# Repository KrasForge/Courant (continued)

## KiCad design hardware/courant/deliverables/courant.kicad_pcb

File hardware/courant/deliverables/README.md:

> **Release synchronization: 2026-09-16.** Current native boards, fabrication-format exports and CAD are indexed in `../../RELEASE_SYNC_STATUS.md`. Earlier statements below about pre-repair exports are historical; electrical/physical validation limitations still apply.

# Current native mainboard — 2026-09-16

| Top (F.Cu, faces the panel) | Bottom (B.Cu) |
| --- | --- |
|  |  |

<sub>Rendered from `courant.kicad_pcb` by `docs/media/scripts/`. Component bodies in the 3D view are simplified stand-ins. See `docs/media/README.md`.</sub>

The PCB in this folder passes Backplane KiCad 10.0.6 DRC: **0 errors, 0 warnings, 0 unconnected**, with unchanged project rules. Current counts: **2,158 track segments and 299 vias**. See `MAINBOARD_REPAIR.md` and `native_checks/drc.json`.

The assembly STEP, mechanical PDF/DXF, `dist/` PCB copies, 2D views, Gerbers, drills, placement data, BOM/netlist metadata and `dist/courant-fab.zip` have been regenerated from the current repaired native board. Use `hardware/refresh_outputs.py` for future review-export refreshes. Legacy route/reconstruction scripts are guarded from overwriting the authoritative native PCB.

**Not a manufacturing approval.** Component/footprint sign-off, FPGA operation/timing, electrical power integrity, thermal/fault behavior and physical assembly remain separate release gates.

The original handoff notes below are preserved as historical information; their old track/via counts are superseded above.

---

# Courant Rev A — handoff package

Standalone Artix-7 instrument board. **160 × 100 mm** on the Edge.Cuts
centreline (160.1 × 100.1 measured over the 0.1 mm stroke), 6 layers, 1.6 mm.
Four NPTH 3.2 mm mounting holes at (25,55), (175,55), (25,145), (175,145) —
150 × 90 mm spacing.
Routed and native-checked: **0 DRC errors, 0 warnings, 0 unconnected**, 2158 track segments,
4386.2 mm of copper, 299 vias, both ground planes uncut.

| File | What it is |
| --- | --- |
| `courant.kicad_pcb` | the board. KiCad 10 |
| `courant.kicad_pro` | project file — **open it alongside the board or you get KiCad's default design rules, not this board's** |
| `courant-assembly.step` | populated assembly, 3D. Board body, copper, silkscreen, soldermask and 183 of 202 component bodies |
| `courant-bom.csv` | bill of materials, 57 line items / 183 placements |
| `courant-netlist.txt` | 96 nets, extracted from the routed board |
| `courant-panel-interface.csv` | pinout of all 15 headers — the spec for building the front panel |
| `courant-mechanical.pdf` | outline, fabrication layer, silkscreen |
| `courant-outline.dxf` | board outline for mechanical CAD |
| `courant-schematic.svg` | schematic — 183 components, 739 pins, 532 wires, 248 net labels, 7038 x 6958 px vector |
| `courant-panel-hardware.md` | off-board parts, with `datasheets/` alongside |
| `courant-eurorack.md` | Eurorack status: what works as built, what changes, with values |
| `courant-source-design.ts` | the design source |

## Design rules

Default 0.15 mm track / 0.15 mm clearance, vias 0.55 / 0.25 mm. Power class
0.40 mm track, Ground 0.30 mm. These are set by the FTG256's 1.0 mm ball pitch:
escaping between two balls needs width + 2 × clearance inside a 0.5 mm gap, and
0.15 + 0.30 = 0.45 mm fits where KiCad's 0.2 mm defaults (0.6 mm) cannot.
0.25 mm drill through 1.6 mm is a 6.4:1 aspect ratio — inside any standard
6-layer process.

## Notes on three of these

**The schematic is rendered by `scripts/schematic.py`, not by tscircuit.**
`tsci export -f schematic-svg` and `-f schematic-pdf` both emit a near-empty
sheet for this design — about ten kilobytes, twenty text elements for two
hundred components — while the circuit JSON behind them holds all 183
components, 739 ports and 532 traces. The data was never missing, only the
drawing, so the drawing is done here. It is complete and to scale; it is not
arranged for signal flow, because tscircuit places symbols in declaration
order and no autolayout turns that into a drafted sheet.

**Every placement has a manufacturer part number**, and each one was checked
against live stock rather than inferred. Two families are covered by one
verified member plus the manufacturer's own value coding, noted on the line:
the Murata C0G run and the Yageo RC0603FR series.

**The panel hardware in `courant-panel-hardware.md` is a proposal.** The design
names no off-board parts and the right ones depend on a panel format that does
not exist yet, so those selections are specified to be electrically correct and
mechanically ordinary — a starting BOM, not a decision already taken. The four
that are sourced have datasheets in `datasheets/`.

## One design fix made while preparing this

R10 was **25 kΩ**, which is on no E-series grid and is not a stocked 1 % part —
a search for it returns 24.9 kΩ. It sets the V1 rail through the TPS62130's
0.8 V reference, so it is now **24.9 kΩ**: 0.8 x (1 + 24.9/100) = 0.9992 V
against a 1.000 V target, nearer than the 1 % resistors can hold. Fixed in
`design.ts` and in the board; `npm run check` passes.

## Before ordering

U1 is **XC7A50T-1FTG256I**, swapped from the XC7A35T-1FTG256C. The pin
compatibility is verified, not assumed: AMD's package files for the two parts
in FTG256 — both kept in `reference/` — are byte-identical from line 2 to the
end. All 256 balls, their banks, I/O types and no-connect flags match; the only
difference in either file is the device name on the header line. That makes the
swap a part number and nothing else, and it is the cheaper part besides
($67.01 against $118.75 at JLCPCB, both in stock) with 57% more logic and an
industrial temperature range.

One check is still worth doing and cannot be done from here: a Vivado synthesis
run against the A50T using the generated `courant_rev_a.xdc`. It will reject
any invalid ball assignment outright, and it confirms timing still closes —
the speed grade is unchanged at -1, so it should.

## Native repair and current files

See `../../REPAIR_STATUS.md` and `../reports/native/`. The local `RadianMain.pretty` snapshots and `fp-lib-table` must travel with the board. Both routed board copies and the manufacturing-format review exports were replaced on 2026-09-16. Native checks are not electrical or physical product validation.

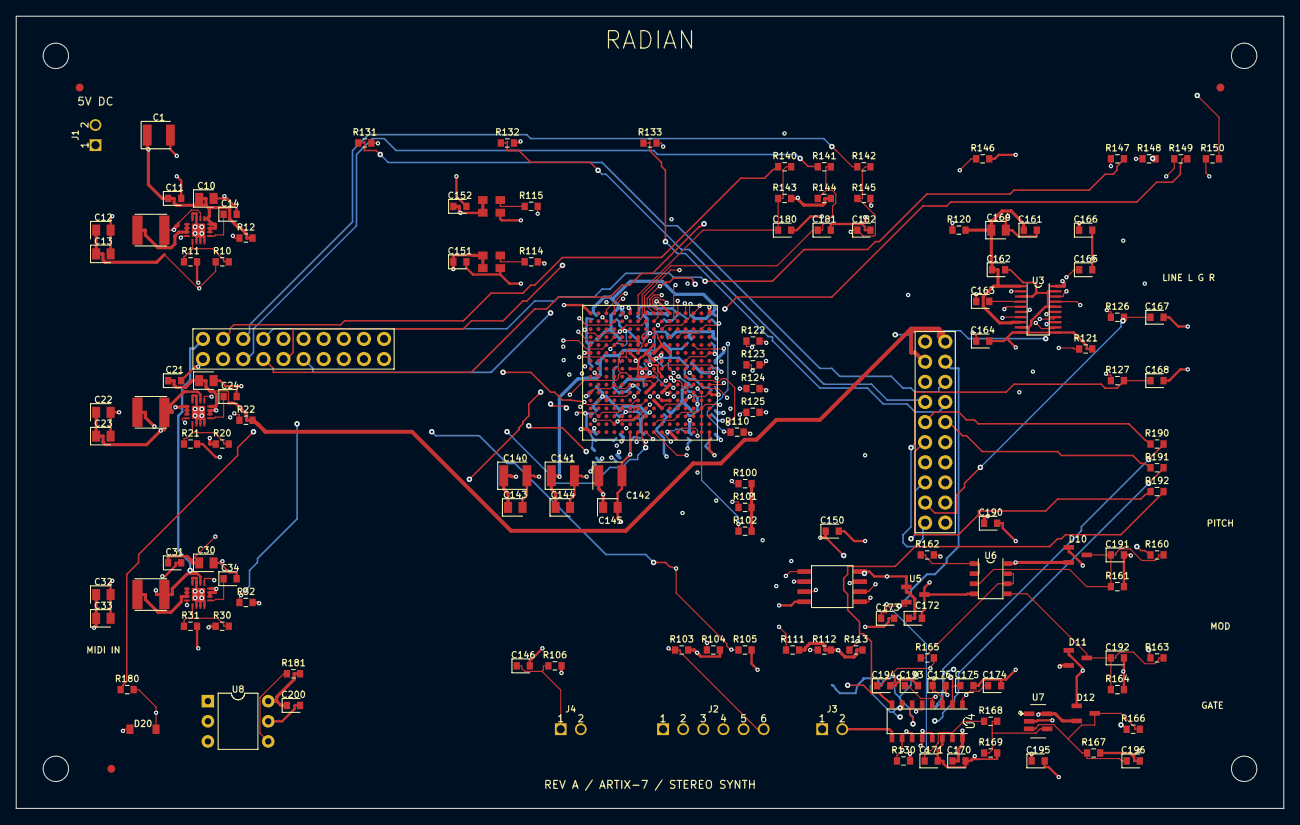
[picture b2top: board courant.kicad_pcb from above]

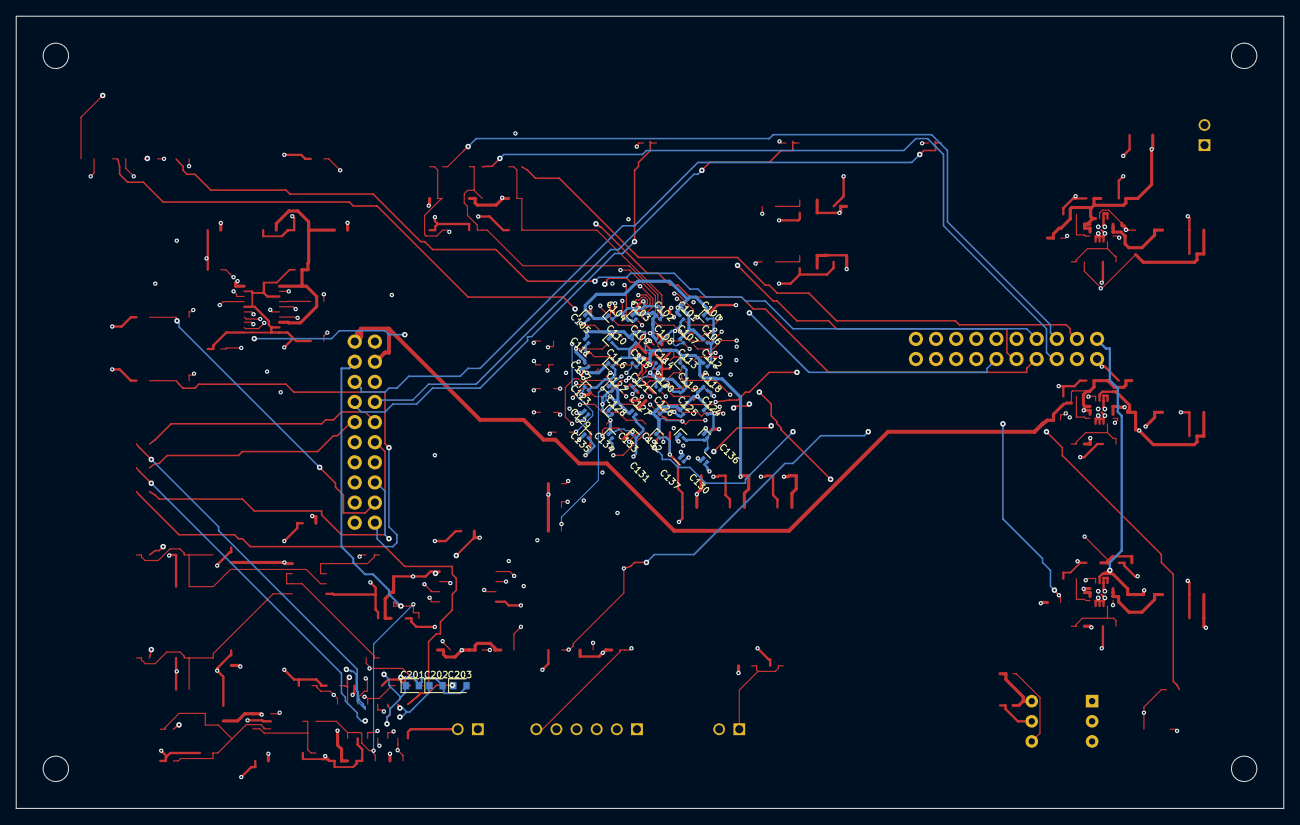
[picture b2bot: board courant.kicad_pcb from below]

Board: 6 copper layers, 160.0 x 100.0 mm, 180 parts (41 on the bottom side), 102 nets.

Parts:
C1, C140, C141: 47uF; C_1210_3225Metric_A
C10, C20, C30, C160: 10uF; C_0805_2012Metric_B
C11, C21, C31, C146, C150, C151, C152, C161, C162, C166, C170, C172, C190, C195, C200: 100nF; C_0603_1608Metric_Radian
C12, C22, C32: 22uF; C_0805_2012Metric_A
C13, C23, C33: 22uF; C_0805_2012Metric_B
C14, C24, C34: 3.3nF; C_0603_1608Metric_Radian
C100, C103, C104, C110, C113, C116, C120, C122, C128: 100nF; C_0201_0603Metric_C
C101, C102, C106, C107, C108, C109, C112, C114, C115, C118, C119, C121, C124, C125, C126, C127, C136: 100nF; C_0201_0603Metric_D
C105, C123, C130, C131, C132, C133, C134, C135: 100nF; C_0201_0603Metric_E
C111, C117, C129: 100nF; C_0201_0603Metric_A
C137: 100nF; C_0201_0603Metric_B
C142: 47uF; C_1210_3225Metric_B
C143, C144: 4.7uF; C_0805_2012Metric_B
C145: 4.7uF; C_0805_2012Metric_A
C163, C164: 2.2uF; C_0603_1608Metric_Radian
C165, C171, C173: 1uF; C_0603_1608Metric_Radian
C167, C168: 2.2nF; C_0603_1608Metric_Radian
C174, C175, C176, C180, C181, C182, C193, C194, C201, C202, C203: 10nF; C_0603_1608Metric_Radian
C191, C192, C196: 1nF; C_0603_1608Metric_Radian
D10, D11, D12: BAT54S; Nexperia_BAT54S_215_SOT23
D20: 1N4148W; Diodes_1N4148W_7_F_SOD123
J1: 22-23-2021; Molex_22_23_2021_RowY
J2: 22-23-2061; Molex_22_23_2061
J3, J4: 22-23-2021; Molex_22_23_2021_RowX
J17, J18: IPT1-110-06-L-D; Samtec_IPT1_110_06_L_D
L1, L2, L3: 1µH; Changjiang_FNR4030S1R0MT
R10: 24.9kΩ; R_0603_1608Metric_Radian
R11, R21, R31, R166: 100kΩ; R_0603_1608Metric_Radian
R12, R22, R32, R103, R104, R105, R106, R121, R130, R143, R144, R145, R146, R169: 10kΩ; R_0603_1608Metric_Radian
R20: 124kΩ; R_0603_1608Metric_Radian
R30: 316kΩ; R_0603_1608Metric_Radian
R100, R101, R102, R111, R112, R113: 4.7kΩ; R_0603_1608Metric_Radian
R110, R114, R115, R122, R123, R124, R125: 33Ω; R_0603_1608Metric_Radian
R120: 1Ω; R_0603_1608Metric_Radian
R126, R127: 470Ω; R_0603_1608Metric_Radian
R131, R132, R133, R140, R141, R142, R147, R148, R149, R150, R190, R191, R192: 1kΩ; R_0603_1608Metric_Radian
R160, R161, R163, R164: 20kΩ; R_0603_1608Metric_Radian
R162, R165: 100Ω; R_0603_1608Metric_Radian
R167: 33kΩ; R_0603_1608Metric_Radian
R168: 40.2kΩ; R_0603_1608Metric_Radian
R180: 220Ω; R_0603_1608Metric_Radian
R181: 2.2kΩ; R_0603_1608Metric_Radian
U1: XC7A50T-1FTG256I; XC7A50T_1FTG256I_FTG256
U2: W25Q64JVSSIQ; W25Q64JVSSIQ_SOIC8_208mil
U3: PCM5102APWR; PCM5102APWR_TSSOP20
U4: MCP3208-CI/SL; MCP3208_CI_SL_SOIC16
U5: REF3125AIDBZR; REF3125AIDBZR_SOT23
U6: MCP6002-I/SN; MCP6002_I_SN_SOIC8
U7: MCP6561T-E/OT; MCP6561T_E_OT_SOT23_5
U8: H11L1M; H11L1M_DIP6
U11, U12, U13: TPS62130ARGTR; TPS62130ARGTR_WQFN16
Y1: ASE-100.000MHZ-LC-T; Abracon_ASE_3225_4Pin
Y2: ASE-12.288MHZ-LC-T; Abracon_ASE_3225_4Pin

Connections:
A3V3: C160.1, C161.1, C162.1, R120.2, U3.1, U3.8
CLK100_RAW: R114.1, Y1.3
DAC_CAPM: C163.2, U3.4
DAC_CAPP: C163.1, U3.2
DAC_L: R126.1, U3.6
DAC_LDO: C165.1, U3.18
DAC_R: R127.1, U3.7
DAC_VNEG: C164.1, U3.5
DONE: R101.1, U1.122
ENC_A_RAW: J18.4, R140.1
ENC_B_RAW: J18.5, R141.1
ENC_SW_RAW: J18.6, R142.1
FB1: R10.2, R11.1, U11.5
FB2: R20.2, R21.1, U12.5
FB3: R30.2, R31.1, U13.5
FLASH_CLK: R110.2, U2.6
FLASH_CLK_RAW: R110.1, U1.72
FLASH_CS: R111.1, U1.172, U2.1
FLASH_HOLD: R113.1, U1.160, U2.7
FLASH_MISO: U1.142, U2.2
FLASH_MOSI: U1.141, U2.5
FLASH_WP: R112.1, U1.159, U2.3
GATE_DIV: C196.1, D12.3, R166.2, R167.1, U7.3
GATE_IN: J17.15, R166.1
GATE_REF: R168.2, R169.1, U7.4
GND: C1.2, C10.2, C11.2, C12.2, C13.2, C14.2, C20.2, C21.2, C22.2, C23.2, C24.2, C30.2, C31.2, C32.2, C33.2, C34.2, C100.2, C101.2, C102.2, C103.2, C104.2, C105.2, C106.2, C107.2, C108.2, C109.2, C110.2, C111.2, C112.2, C113.2, C114.2, C115.2, C116.2, C117.2, C118.2, C119.2, C120.2, C121.2, C122.2, C123.2, C124.2, C125.2, C126.2, C127.2, C128.2, C129.2, C130.2, C131.2, C132.2, C133.2, C134.2, C135.2, C136.2, C137.2, C140.2, C141.2, C142.2, C143.2, C144.2, C145.2, C146.2, C150.2, C151.2, C152.2, C160.2, C161.2, C162.2, C164.2, C165.2, C166.2, C167.2, C168.2, C170.2, C171.2, C172.2, C173.2, C174.2, C175.2, C176.2, C180.2, C181.2, C182.2, C190.2, C191.2, C192.2, C193.2, C194.2, C195.2, C196.2, C200.2, C201.2, C202.2, C203.2, D10.1, D11.1, D12.1, J1.2, J2.2, J3.2, J4.2, J17.1, J17.5, J17.12, J17.16, J17.18, J17.20, J18.1, J18.3, J18.12, R11.2, R21.2, R31.2, R105.2, R121.2, R146.2, R161.2, R164.2, R167.2, R169.2, U1.1, U1.11, U1.24, U1.37, U1.47, U1.50, U1.60, U1.73, U1.86, U1.88, U1.90, U1.96, U1.99, U1.103, U1.105, U1.109, U1.118, U1.119, U1.120, U1.135, U1.136, U1.137, U1.139, U1.148, U1.150, U1.158, U1.161, U1.171, U1.184, U1.186, U1.187, U1.197, U1.207, U1.210, U1.220, U1.233, U1.246, U1.256, U2.4, U3.3, U3.9, U3.10, U3.11, U3.16, U3.19, U4.9, U4.14, U5.3, U6.4, U7.2, U8.5, U11.6, U11.7, U11.8, U11.15, U11.16, U11.17, U12.6, U12.7, U12.8, U12.15, U12.16, U12.17, U13.6, U13.7, U13.8, U13.15, U13.16, U13.17, Y1.2, Y2.2
I2S_BCLK: R123.2, U3.13
I2S_DATA: R125.2, U3.14
I2S_LRCLK: R124.2, U3.15
I2S_MCLK: R122.2, U3.12
INIT_B: R100.1, U1.154
JTAG_TCK: J2.3, J18.17, R105.1, U1.167
JTAG_TDI: J2.5, J18.19, R104.1, U1.199
JTAG_TDO: J2.4, J18.18, U1.200
JTAG_TMS: J2.6, J18.20, R103.1, U1.183
LED0_A: J18.8, R147.2
LED1_A: J18.9, R148.2
LED2_A: J18.10, R149.2
LED3_A: J18.11, R150.2
LINE_L: C167.1, J17.17, R126.2
LINE_R: C168.1, J17.19, R127.2
MCLK_RAW: R115.1, Y2.3
MIDI4: J18.13, R180.1
MIDI5: D20.1, J18.14, U8.2
MIDI_A: D20.2, R180.2, U8.1
MOD_ADC: C194.1, R165.2, U4.5
MOD_BUF: R165.1, U6.6, U6.7
MOD_DIV: C192.1, D11.3, R163.2, R164.1, U6.5
MOD_IN: J17.14, R163.1
PG1: R12.1, U11.4, U12.13
PG18: R22.1, U12.4, U13.13
PITCH_ADC: C193.1, R162.2, U4.4
PITCH_BUF: R162.1, U6.1, U6.2
PITCH_DIV: C191.1, D10.3, R160.2, R161.1, U6.3
PITCH_IN: J17.13, R160.1
POT_DECAY: C175.1, R132.2, U4.2
POT_DECAY_RAW: J17.7, R132.1
POT_DELAY: C202.1, R191.2, U4.7
POT_DELAY_RAW: J17.10, R191.1
POT_DRIVE: C201.1, R190.2, U4.6
POT_DRIVE_RAW: J17.9, R190.1
POT_PITCH: C174.1, R131.2, U4.1
POT_PITCH_RAW: J17.6, R131.1
POT_REVERB: C203.1, R192.2, U4.8
POT_REVERB_RAW: J17.11, R192.1
POT_TIMBRE: C176.1, R133.2, U4.3
POT_TIMBRE_RAW: J17.8, R133.1
PROGRAM_B: J3.1, J18.15, R32.1, U1.169, U13.4
PUDC_B: R102.1, U1.175
SS1: C14.1, U11.9
SS2: C24.1, U12.9
SS3: C34.1, U13.9
SW1: L1.1, U11.1, U11.2, U11.3
SW2: L2.1, U12.1, U12.2, U12.3
SW3: L3.1, U13.1, U13.2, U13.3
V1: C12.1, C13.1, C100.1, C101.1, C102.1, C103.1, C104.1, C105.1, C106.1, C107.1, C108.1, C140.1, C143.1, L1.2, R10.1, U1.74, U1.87, U1.89, U1.91, U1.102, U1.121, U1.134, U1.153, U1.168, U11.14
V1V8: C22.1, C23.1, C109.1, C110.1, C111.1, C112.1, C113.1, C141.1, C144.1, L2.2, R20.1, U1.104, U1.106, U1.138, U1.155, U1.170, U12.14
V3V3: C32.1, C33.1, C114.1, C115.1, C116.1, C117.1, C118.1, C119.1, C120.1, C121.1, C122.1, C123.1, C124.1, C125.1, C126.1, C127.1, C128.1, C129.1, C130.1, C131.1, C132.1, C133.1, C134.1, C135.1, C136.1, C137.1, C142.1, C145.1, C150.1, C151.1, C152.1, C166.1, C170.1, C172.1, C190.1, C195.1, C200.1, D10.2, D11.2, D12.2, J2.1, J18.2, L3.2, R30.1, R32.2, R100.2, R101.2, R102.2, R103.2, R104.2, R106.2, R111.2, R112.2, R113.2, R120.1, R130.2, R143.2, R144.2, R145.2, R181.2, U1.6, U1.16, U1.19, U1.29, U1.42, U1.55, U1.68, U1.71, U1.78, U1.81, U1.127, U1.130, U1.140, U1.166, U1.176, U1.179, U1.185, U1.189, U1.202, U1.215, U1.228, U1.238, U1.241, U1.251, U2.8, U3.20, U4.16, U5.1, U6.8, U7.5, U8.6, U13.14, Y1.1, Y1.4, Y2.1, Y2.4
VIN5: C1.1, C10.1, C11.1, C20.1, C21.1, C30.1, C31.1, J1.1, J17.2, J17.3, R12.2, R22.2, U11.10, U11.11, U11.12, U11.13, U12.10, U12.11, U12.12, U13.10, U13.11, U13.12
VREF25: C171.1, C173.1, J17.4, R168.1, U4.15, U5.2
adc_cs_n: R130.1, U1.5, U4.10
adc_miso: U1.4, U4.12
adc_mosi: U1.20, U4.11
adc_sclk: U1.3, U4.13
audio_mclk_in: R115.2, U1.67
clk100: R114.2, U1.52
cv_select: J18.7, R146.1, U1.9
dac_bclk: R123.1, U1.248
dac_data: R125.1, U1.250
dac_lrclk: R124.1, U1.249
dac_mclk: R122.1, U1.247
dac_unmute: R121.1, U1.252, U3.17
enc_a: C180.1, R140.2, R143.1, U1.7
enc_b: C181.1, R141.2, R144.1, U1.23
enc_btn_n: C182.1, R142.2, R145.1, U1.8
gate: U1.10, U7.1
led0: R147.1, U1.12
led1: R148.1, U1.28
led2: R149.1, U1.13
led3: R150.1, U1.14
midi_rx: R181.1, U1.25, U8.4
reset_n: C146.1, J4.1, J18.16, R106.1, U1.26

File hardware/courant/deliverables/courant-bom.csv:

Reference(s),Qty,Value,Footprint,Side,Manufacturer,MPN,LCSC,Notes
"C101,C102,C106,C107,C108,C109,C112,C114,C115,C118,C119,C121,C124,C125,C126,C127,C136",17,100nF,RadianMain:C_0201_0603Metric_D,bottom,CCTC,TCC0201X5R104K100ZT,C5142565,10 V X5R. JLC extended library: one setup fee for the whole array
"C11,C21,C31,C146,C150,C151,C152,C161,C162,C166,C170,C172,C190,C195,C200",15,100nF,RadianMain:C_0603_1608Metric_Radian,top,Samsung,CL10B104KB8NNNC,C1591,50 V X7R
"R12,R22,R32,R103,R104,R105,R106,R121,R130,R143,R144,R145,R146,R169",14,10kΩ,RadianMain:R_0603_1608Metric_Radian,top,Yageo,RC0603FR-0710KL,C98220,thick film 1%
"R131,R132,R133,R140,R141,R142,R147,R148,R149,R150,R190,R191,R192",13,1kΩ,RadianMain:R_0603_1608Metric_Radian,top,Yageo,RC0603FR-071KL,,thick film 1%
"C100,C103,C104,C110,C113,C116,C120,C122,C128",9,100nF,RadianMain:C_0201_0603Metric_C,bottom,CCTC,TCC0201X5R104K100ZT,C5142565,10 V X5R. JLC extended library: one setup fee for the whole array
"C105,C123,C130,C131,C132,C133,C134,C135",8,100nF,RadianMain:C_0201_0603Metric_E,bottom,CCTC,TCC0201X5R104K100ZT,C5142565,10 V X5R. JLC extended library: one setup fee for the whole array
"C174,C175,C176,C180,C181,C182,C193,C194",8,10nF,RadianMain:C_0603_1608Metric_Radian,top,Murata,GRM1885C1H103JA01D,C85973,"50 V C0G -- ADC anti-alias, C0G for low voltage coefficient"
"R110,R114,R115,R122,R123,R124,R125",7,33Ω,RadianMain:R_0603_1608Metric_Radian,top,Yageo,RC0603FR-0733RL,,thick film 1%
"R100,R101,R102,R111,R112,R113",6,4.7kΩ,RadianMain:R_0603_1608Metric_Radian,top,Yageo,RC0603FR-074K7L,,thick film 1%
"R11,R21,R31,R166",4,100kΩ,RadianMain:R_0603_1608Metric_Radian,top,Yageo,RC0603FR-07100KL,,thick film 1%
"C10,C20,C30,C160",4,10uF,RadianMain:C_0805_2012Metric_B,top,Samsung,CL21A106KAYNNNE,C15850,"25 V X5R, JLC basic library"
"R160,R161,R163,R164",4,20kΩ,RadianMain:R_0603_1608Metric_Radian,top,Yageo,RT0603BRD0720KL,C723637,"0.1%, 25 ppm/C thin film -- matched CV divider pair"
"C111,C117,C129",3,100nF,RadianMain:C_0201_0603Metric_A,bottom,CCTC,TCC0201X5R104K100ZT,C5142565,10 V X5R. JLC extended library: one setup fee for the whole array
"C201,C202,C203",3,10nF,RadianMain:C_0603_1608Metric_Radian,bottom,Murata,GRM1885C1H103JA01D,C85973,"50 V C0G -- ADC anti-alias, C0G for low voltage coefficient"
"C191,C192,C196",3,1nF,RadianMain:C_0603_1608Metric_Radian,top,Murata,GRM1885C1H102JA01D,,"50 V C0G, same series as the 10 nF"
"C165,C171,C173",3,1uF,RadianMain:C_0603_1608Metric_Radian,top,Samsung,CL10B105KB8NQNC,C5199872,50 V X7R
"L1,L2,L3",3,1µH,RadianMain:Changjiang_FNR4030S1R0MT,top,Changjiang Electronics,FNR4030S1R0MT,C167865,"4x4 mm shielded, 18 mOhm, 5.7 A sat -- must exceed the TPS62130's 3 A plus ripple"
"C13,C23,C33",3,22uF,RadianMain:C_0805_2012Metric_B,top,Samsung,CL21A226MAQNNNE,C45783,"25 V X5R, JLC basic library -- switcher output"
"C12,C22,C32",3,22uF,RadianMain:C_0805_2012Metric_A,top,Samsung,CL21A226MAQNNNE,C45783,"25 V X5R, JLC basic library -- switcher output"
"C14,C24,C34",3,3.3nF,RadianMain:C_0603_1608Metric_Radian,top,Murata,GRM1885C1H332JA01D,,50 V C0G -- switcher soft-start
"C1,C140,C141",3,47uF,RadianMain:C_1210_3225Metric_A,top,Murata,GRM32ER61C476KE15L,C77101,16 V X5R -- bulk input
"D10,D11,D12",3,BAT54S,RadianMain:Nexperia_BAT54S_215_SOT23,top,Nexperia,"BAT54S,215",,"Nexperia BAT54S,215; SOT-23 dual Schottky diode"
"U11,U12,U13",3,TPS62130ARGTR,RadianMain:TPS62130ARGTR_WQFN16,top,Texas Instruments,TPS62130ARGTR,,"3 A buck, QFN-16 with exposed pad"
"R162,R165",2,100Ω,RadianMain:R_0603_1608Metric_Radian,top,Yageo,RC0603FR-07100RL,,thick film 1%
"C167,C168",2,2.2nF,RadianMain:C_0603_1608Metric_Radian,top,Murata,GRM1885C1H222JA01D,,"50 V C0G, same series"
"C163,C164",2,2.2uF,RadianMain:C_0603_1608Metric_Radian,top,Samsung,CL10A225KO8NNNC,C23630,"16 V X5R, JLC basic library"
"C143,C144",2,4.7uF,RadianMain:C_0805_2012Metric_B,top,Yageo,CC0805KKX7R8BB475,C354262,25 V X7R
"R126,R127",2,470Ω,RadianMain:R_0603_1608Metric_Radian,top,Yageo,RC0603FR-07470RL,,thick film 1%
"J17,J18",2,IPT1-110-06-L-D,RadianMain:Samtec_IPT1_110_06_L_D,top,Samtec,IPT1-110-06-L-D,,2x10 2.54 mm vertical through-hole terminal strip; mates IPS1-110-01-L-D. Fully-mated PCB gap 19.99 mm; 20.45 mm max.
C137,1,100nF,RadianMain:C_0201_0603Metric_B,bottom,CCTC,TCC0201X5R104K100ZT,C5142565,10 V X5R. JLC extended library: one setup fee for the whole array
R20,1,124kΩ,RadianMain:R_0603_1608Metric_Radian,top,Yageo,RC0603FR-07124KL,,thick film 1%
D20,1,1N4148W,RadianMain:Diodes_1N4148W_7_F_SOD123,top,Diodes Incorporated,1N4148W-7-F,,Diodes Incorporated 1N4148W-7-F; SOD-123 fast switching diode
"J4,J3",2,22-23-2021,RadianMain:Molex_22_23_2021_RowX,top,Molex,22-23-2021,,KK 254 vertical friction-lock. Harness side: housing 22-01-3027 + 2 x 08-55-0102 crimp terminals
J1,1,22-23-2021,RadianMain:Molex_22_23_2021_RowY,top,Molex,22-23-2021,,KK 254 vertical friction-lock. Harness side: housing 22-01-3027 + 2 x 08-55-0102 crimp terminals
J2,1,22-23-2061,RadianMain:Molex_22_23_2061,top,Molex,22-23-2061,,KK 254 vertical friction-lock. Harness side: housing 22-01-3067 + 6 x 08-55-0102 crimp terminals
R120,1,1Ω,RadianMain:R_0603_1608Metric_Radian,top,Yageo,RC0603FR-071RL,,thick film 1%
R181,1,2.2kΩ,RadianMain:R_0603_1608Metric_Radian,top,Yageo,RC0603FR-072K2L,,thick film 1%
R180,1,220Ω,RadianMain:R_0603_1608Metric_Radian,top,Yageo,RC0603FR-07220RL,,thick film 1%
R10,1,24.9kΩ,RadianMain:R_0603_1608Metric_Radian,top,Yageo,RC0603FR-0724K9L,C137761,thick film 1%
R30,1,316kΩ,RadianMain:R_0603_1608Metric_Radian,top,Yageo,RC0603FR-07316KL,,thick film 1%
R167,1,33kΩ,RadianMain:R_0603_1608Metric_Radian,top,Yageo,RC0603FR-0733KL,,thick film 1%
C145,1,4.7uF,RadianMain:C_0805_2012Metric_A,top,Yageo,CC0805KKX7R8BB475,C354262,25 V X7R
R168,1,40.2kΩ,RadianMain:R_0603_1608Metric_Radian,top,Yageo,RC0603FR-0740K2L,,thick film 1%
C142,1,47uF,RadianMain:C_1210_3225Metric_B,top,Murata,GRM32ER61C476KE15L,C77101,16 V X5R -- bulk input
Y1,1,ASE-100.000MHZ-LC-T,RadianMain:Abracon_ASE_3225_4Pin,top,Abracon,ASE-100.000MHZ-LC-T,,100 MHz system oscillator
Y2,1,ASE-12.288MHZ-LC-T,RadianMain:Abracon_ASE_3225_4Pin,top,Abracon,ASE-12.288MHZ-LC-T,,12.288 MHz audio master clock
U8,1,H11L1M,RadianMain:H11L1M_DIP6,top,onsemi,H11L1M,,"Schmitt optocoupler, MIDI input"
U4,1,MCP3208-CI/SL,RadianMain:MCP3208_CI_SL_SOIC16,top,Microchip,MCP3208-CI/SL,,8-ch 12-bit SPI ADC
U6,1,MCP6002-I/SN,RadianMain:MCP6002_I_SN_SOIC8,top,Microchip,MCP6002-I/SN,,"dual op-amp, CV buffer"
U7,1,MCP6561T-E/OT,RadianMain:MCP6561T_E_OT_SOT23_5,top,Microchip,MCP6561T-E/OT,,"comparator, gate input"
U3,1,PCM5102APWR,RadianMain:PCM5102APWR_TSSOP20,top,Texas Instruments,PCM5102APWR,,stereo audio DAC
U5,1,REF3125AIDBZR,RadianMain:REF3125AIDBZR_SOT23,top,Texas Instruments,REF3125AIDBZR,,2.5 V reference
U2,1,W25Q64JVSSIQ,RadianMain:W25Q64JVSSIQ_SOIC8_208mil,top,Winbond,W25Q64JVSSIQ,,64 Mbit SPI flash
U1,1,XC7A50T-1FTG256I,RadianMain:XC7A50T_1FTG256I_FTG256,top,AMD/Xilinx,XC7A50T-1FTG256I,C3272410,"FPGA, 52160 logic cells, industrial temp"

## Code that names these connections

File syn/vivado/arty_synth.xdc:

# arty_synth.xdc - constraints for arty_synth (synth_top board build, issue #76)
#
# Digilent Arty A7 + Pmod I2S2 (on Pmod header JA). The system and audio clocks
# are generated by the on-board MMCM from the 100 MHz oscillator, so only the
# 100 MHz input is a primary clock; sys_clk / mclk are derived automatically.
# The serial bit clock BCLK is divided from mclk in fabric by i2s_clkgen, so it
# is declared as a generated clock and the mesh (sys_clk) / audio (bclk) domains
# are constrained as an asynchronous crossing (matching arty_a7.xdc).

#==============================================================================
# Primary clock: 100 MHz oscillator
#==============================================================================
set_property -dict { PACKAGE_PIN E3 IOSTANDARD LVCMOS33 } [get_ports clk100]
create_clock -name clk100 -period 10.000 [get_ports clk100]

#==============================================================================
# Buttons / switches (reset + preset controls)
#==============================================================================
## btn0 reset, btn1 preset recall, btn2 preset save
set_property -dict { PACKAGE_PIN D9  IOSTANDARD LVCMOS33 } [get_ports {btn[0]}]
set_property -dict { PACKAGE_PIN C9  IOSTANDARD LVCMOS33 } [get_ports {btn[1]}]
set_property -dict { PACKAGE_PIN B9  IOSTANDARD LVCMOS33 } [get_ports {btn[2]}]
set_property -dict { PACKAGE_PIN B8  IOSTANDARD LVCMOS33 } [get_ports {btn[3]}]
## slide switches -> preset index
set_property -dict { PACKAGE_PIN A8  IOSTANDARD LVCMOS33 } [get_ports {sw[0]}]
set_property -dict { PACKAGE_PIN C11 IOSTANDARD LVCMOS33 } [get_ports {sw[1]}]
set_property -dict { PACKAGE_PIN C10 IOSTANDARD LVCMOS33 } [get_ports {sw[2]}]
set_property -dict { PACKAGE_PIN A10 IOSTANDARD LVCMOS33 } [get_ports {sw[3]}]
## active-voice LEDs
set_property -dict { PACKAGE_PIN H5  IOSTANDARD LVCMOS33 } [get_ports {led[0]}]
set_property -dict { PACKAGE_PIN J5  IOSTANDARD LVCMOS33 } [get_ports {led[1]}]
set_property -dict { PACKAGE_PIN T9  IOSTANDARD LVCMOS33 } [get_ports {led[2]}]
set_property -dict { PACKAGE_PIN T10 IOSTANDARD LVCMOS33 } [get_ports {led[3]}]

#==============================================================================
# Pmod I2S2 codec (Pmod header JA) + MIDI in
#==============================================================================
## JA1 MCLK, JA2 LRCLK, JA3 BCLK, JA4 SDIN (to DAC)
set_property -dict { PACKAGE_PIN G13 IOSTANDARD LVCMOS33 } [get_ports codec_mclk]
set_property -dict { PACKAGE_PIN B11 IOSTANDARD LVCMOS33 } [get_ports codec_lrclk]
set_property -dict { PACKAGE_PIN A11 IOSTANDARD LVCMOS33 } [get_ports codec_bclk]
set_property -dict { PACKAGE_PIN D12 IOSTANDARD LVCMOS33 } [get_ports codec_sdin]
## serial MIDI in (opto-isolated 31250 baud) on JA7
set_property -dict { PACKAGE_PIN D13 IOSTANDARD LVCMOS33 } [get_ports midi_rx]

## front-panel rotary encoder + CV gate (Pmod JB GPIO)
set_property -dict { PACKAGE_PIN E15 IOSTANDARD LVCMOS33 } [get_ports enc_a]
set_property -dict { PACKAGE_PIN E16 IOSTANDARD LVCMOS33 } [get_ports enc_b]
set_property -dict { PACKAGE_PIN D15 IOSTANDARD LVCMOS33 } [get_ports enc_btn]
set_property -dict { PACKAGE_PIN C15 IOSTANDARD LVCMOS33 } [get_ports gate]
set_false_path -from [get_ports {enc_a enc_b enc_btn gate}]

## NOTE: the pot / CV analog samples (pot_pitch/decay/timbre, pitch_cv, mod_cv)
## are digital *sample* ports fed by an XADC or an external SPI/I2S ADC block,
## which is out of scope for this build. Wire them to that ADC's outputs (and
## constrain the ADC's own pins) when it is added; they are left unconstrained
## here so the panel/CV integration synthesises without a placeholder ADC.
set_property SEVERITY {Warning} [get_drc_checks NSTD-1]
set_property SEVERITY {Warning} [get_drc_checks UCIO-1]

#==============================================================================
# Clock-domain crossing (mesh sys_clk  <->  audio bclk)
#==============================================================================
# BCLK is mclk/4, produced by i2s_clkgen in fabric; declare it as a generated
# clock so the tools see the audio domain. (Adjust the source pin/net name to
# the elaborated design if the auto-inference does not pick it up.)
create_generated_clock -name bclk -source [get_pins -hier -filter {NAME =~ *i2s_clkgen*bclk_i_reg*/C}] \
  -divide_by 4 [get_pins -hier -filter {NAME =~ *i2s_clkgen*bclk_i_reg*/Q}]

# The mesh (sys_clk) and audio (bclk) domains are independent: cut setup/hold on
# the crossing (the cdc_word MCP handshake relies on this) and bound the
# multi-bit pickup word's skew so it cannot tear.
set_clock_groups -asynchronous \
  -group [get_clocks -include_generated_clocks clk100] \
  -group [get_clocks bclk]

set_bus_skew -from [get_cells -hierarchical -filter {NAME =~ *cdc_pick/hold_reg*}] \
             -to   [get_cells -hierarchical -filter {NAME =~ *cdc_pick/dst_data_reg*}] 81.380

# Asynchronous inputs (buttons, MIDI): do not time their capture edge.
set_false_path -from [get_ports {btn[*] sw[*] midi_rx}]

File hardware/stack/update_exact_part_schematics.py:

#!/usr/bin/env python3
from pathlib import Path
import re
D=Path('/home/ik/ChatGPT/Courant/hardware/panel/design')

def replace_count(path,old,new,count):
    p=D/path;s=p.read_text();n=s.count(old)
    if n!=count: raise RuntimeError(f'{path}: {old!r} count {n}, expected {count}')
    p.write_text(s.replace(old,new))
    return n

# Exact drop-in production connectors.
replace_count('power.kicad_sch','"EURORACK 10 PIN"','"61201021621"',2)
replace_count('power.kicad_sch','"RadianPanel:IDC_2x05_P2.54_Shrouded"','"RadianPanel:Wurth_61201021621_Exact_B"',2)
replace_count('power.kicad_sch','"SELECT keyed 2x05 IDC 2.54 mm header"','"61201021621"',1)

replace_count('power.kicad_sch','"DESKTOP 12 V INPUT"','"22-27-2021"',2)
replace_count('power.kicad_sch','"RadianPanel:Header_1x02_P2.54"','"RadianPanel:Molex_22-27-2021_J201_B"',2)
replace_count('power.kicad_sch','"SELECT locking 2-pin >=2A connector; P2.54 footprint"','"22-27-2021"',1)

replace_count('io.kicad_sch','"TO OFF-BOARD MIDI DIN"','"22-27-2021"',2)
replace_count('io.kicad_sch','"RadianPanel:Header_1x02_P2.54"','"RadianPanel:Molex_22-27-2021_J306_B"',2)
replace_count('io.kicad_sch','"SELECT 2.54 mm 1x02 header"','"22-27-2021"',1)

replace_count('service.kicad_sch','"JTAG SERVICE"','"22-27-2061"',2)
replace_count('service.kicad_sch','"RadianPanel:Header_1x06_P2.54"','"RadianPanel:Molex_22-27-2061_J202_B"',2)
replace_count('service.kicad_sch','"SELECT 2.54 mm 1x06 header"','"22-27-2061"',1)

# JP1: actual Wurth SPDT pinout. Old schematic positions top/middle/bottom were
# pins 1/2/3 = MOD_RAW/MOD_IN/MOD_BIPOLAR. Actual switch is:
# pin 3 = top MOD_RAW, pin 1 = middle common MOD_IN, pin 2 = bottom MOD_BIPOLAR.
p=D/'mod.kicad_sch';s=p.read_text()
s=s.replace('"MOD RANGE: 1-2 UNI / 2-3 BI"','"450301014042"')
s=s.replace('"RadianPanel:Header_1x03_P2.54"','"RadianPanel:Wurth_450301014042_Exact_B"')
s=s.replace('"2.54 mm 1x03 header + removable shunt"','"450301014042"')
# Symbol definition: edit the three pins by their fixed locations.
start=s.index('(symbol "JP1_1_1"'); end=s.index('(property "Description"',start)
block=s[start:end]
for at,num in [('(at -12.7 2.54 0)','3'),('(at -12.7 0.0 0)','1'),('(at -12.7 -2.54 0)','2')]:
    i=block.index(at); j=block.find('(pin passive line',i+1); j=len(block) if j<0 else j
    seg=block[i:j]
    seg=re.sub(r'\(name "[123]"',f'(name "{num}"',seg)
    seg=re.sub(r'\(number "[123]"',f'(number "{num}"',seg)
    block=block[:i]+seg+block[j:]
s=s[:start]+block+s[end:]
# Instance pin UUIDs follow the same fixed graphical positions.
mapping={
 '031fc1de-f652-56e7-993b-2ddd33f1cf5b':'3',
 'a988563f-0536-5d32-9cf9-0b06dc0ab031':'1',
 '4b7ea1de-3e57-5a72-ba4b-1ca26cb4b4f4':'2'}
for uid,num in mapping.items():
    s=re.sub(r'\(pin "[123]"\s*\(uuid "'+re.escape(uid)+r'"\)\)',f'(pin "{num}"\n      (uuid "{uid}"))',s,count=1)
s=s.replace('DEFAULT: shunt JP1 pins 1-2 = direct unipolar MOD; preserve existing firmware interpretation.',
            'JP1 is an SPDT configuration switch: one throw selects direct unipolar MOD_RAW; the other selects MOD_BIPOLAR.')
p.write_text(s)
print('schematics updated for exact service parts')
